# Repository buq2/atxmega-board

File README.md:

# atxmega-board

Simple pcb for atmel atxmega

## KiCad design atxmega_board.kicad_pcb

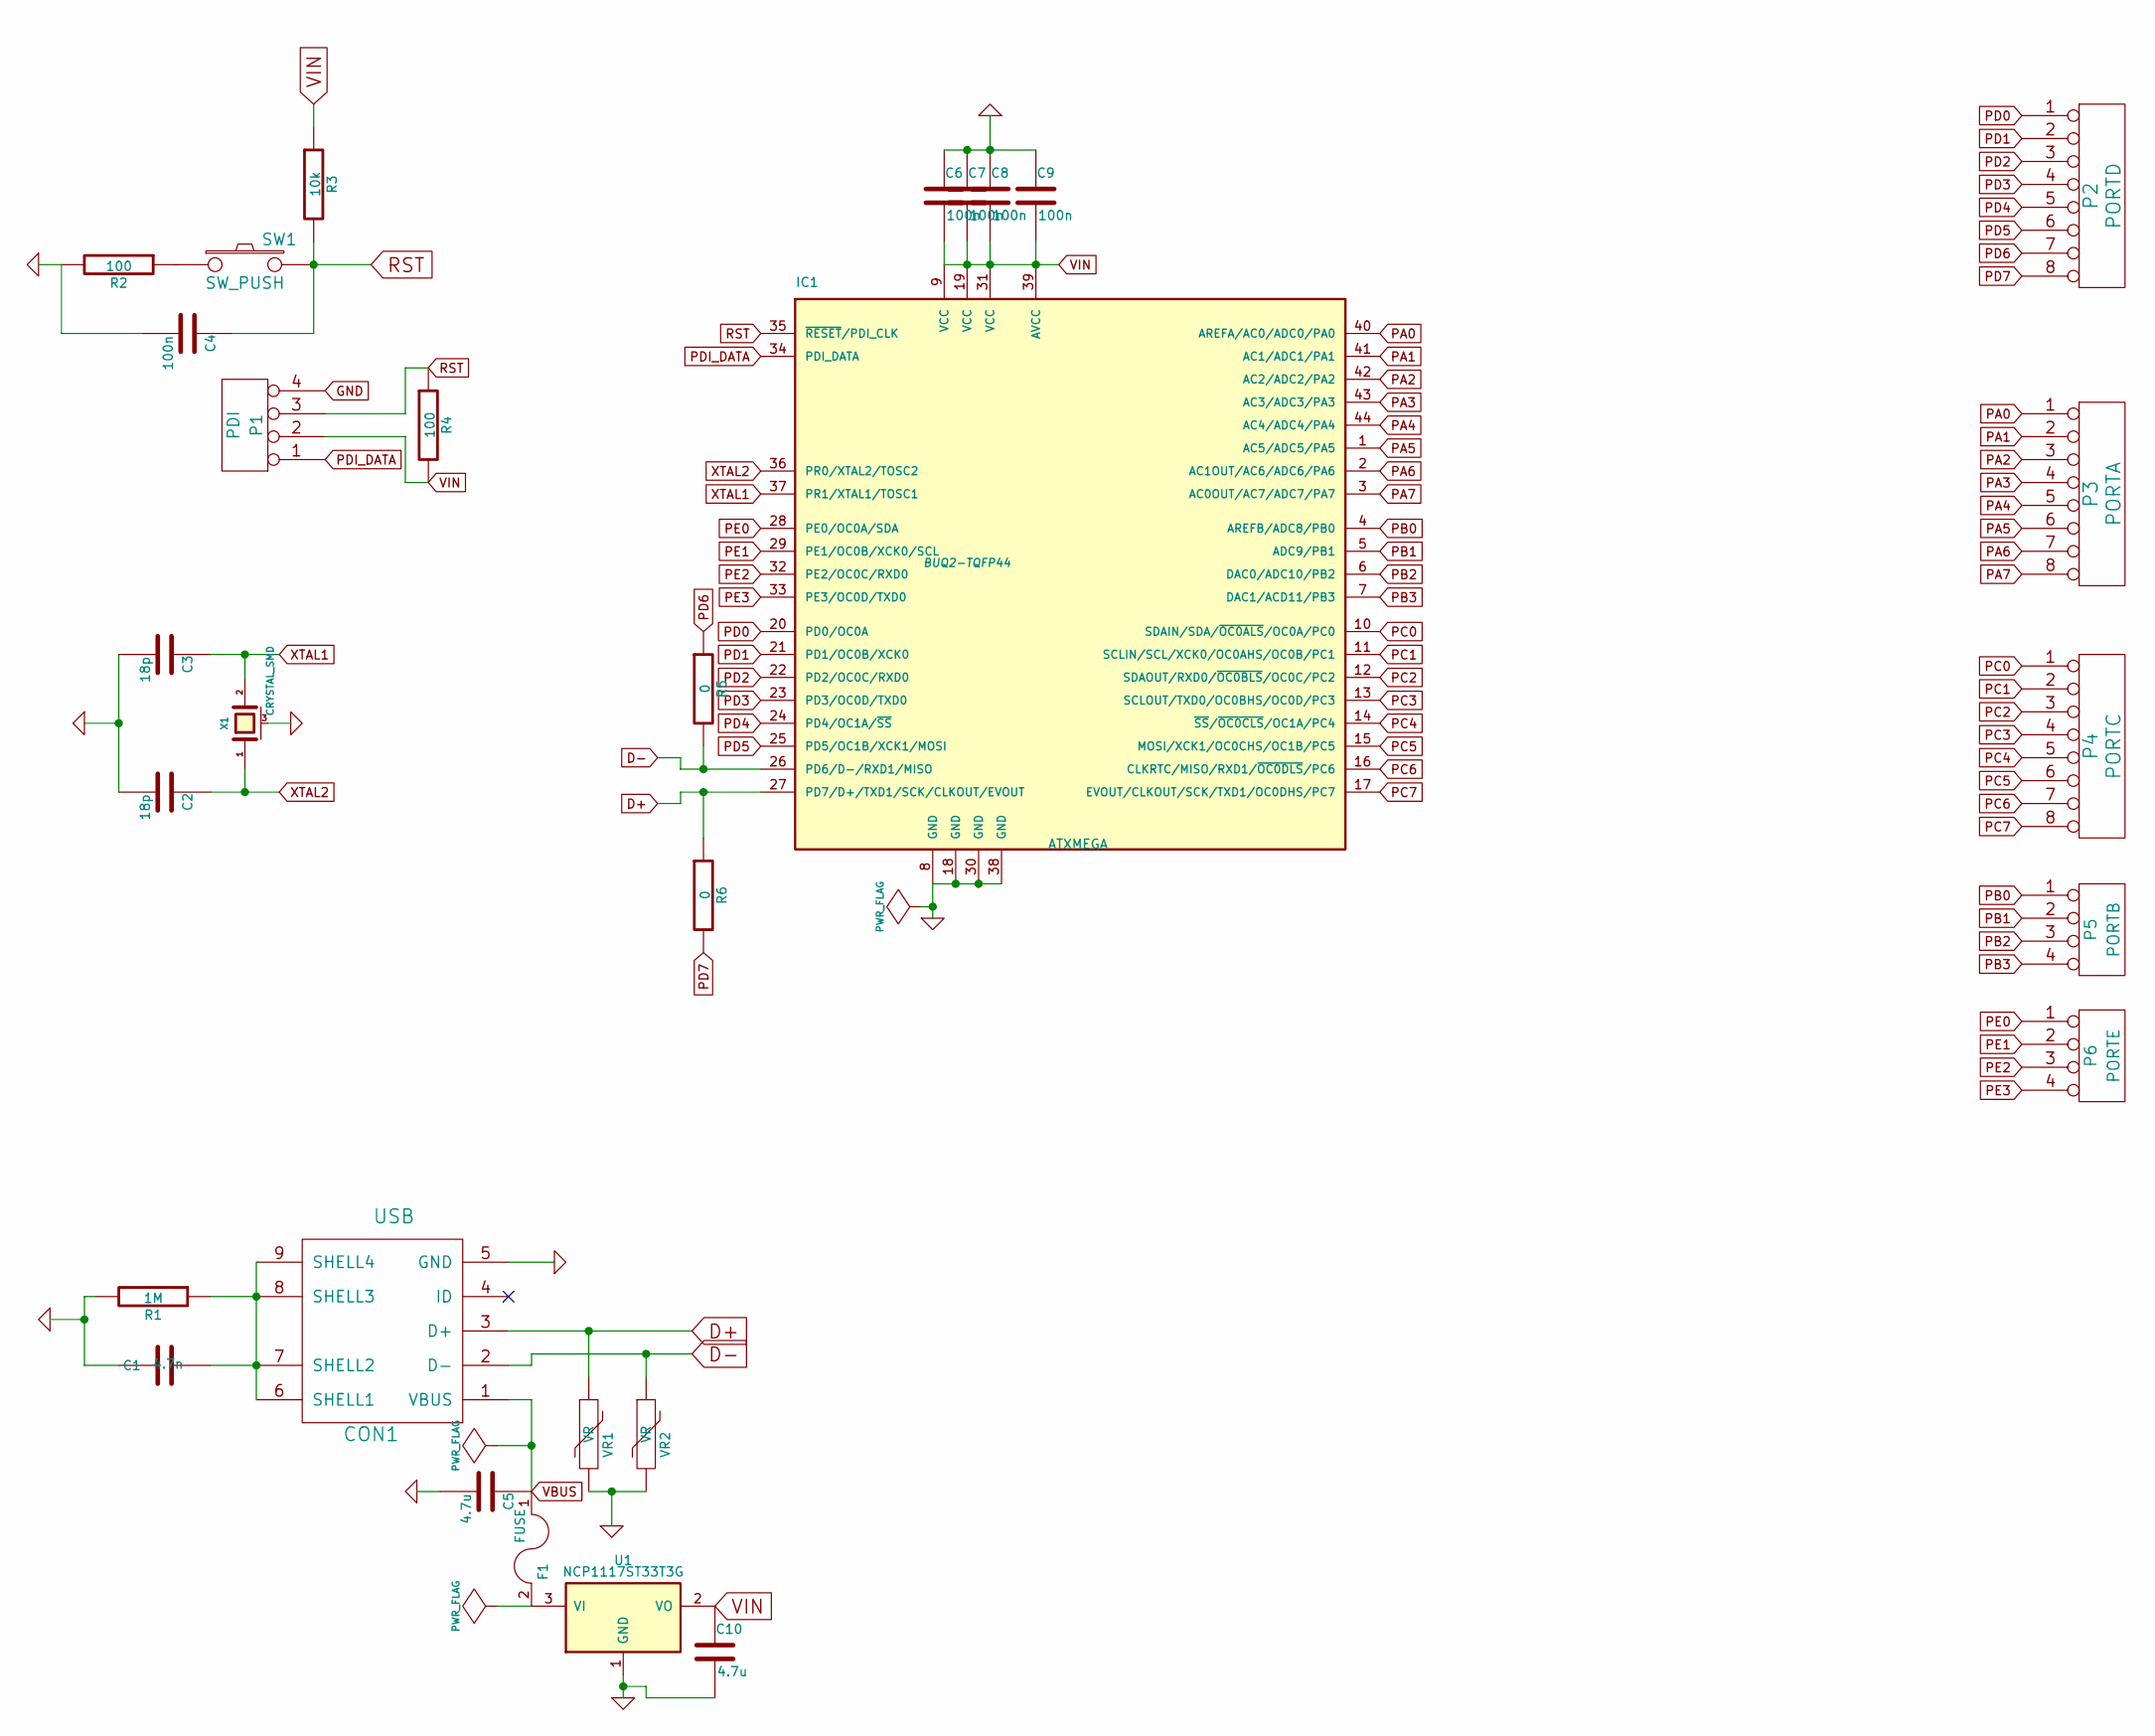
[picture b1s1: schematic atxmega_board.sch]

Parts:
C1: 4.7n; SM0603
C2, C3: 18p
C4, C6, C7, C8, C9: 100n; SM0603
C5, C10: 4.7u; SM0805
CON1: USB; BUQ2-USB-B-RIGHT-ANGLE-SM; Digikey 151-1206-1-ND
F1: FUSE
IC1: ATXMEGA; BUQ2-TQFP44
P1: PDI
P2: PORTD
P3: PORTA
P4: PORTC
P5: PORTB
P6: PORTE
R1: 1M; SM0603
R2, R4: 100; SM0603
R3: 10k; SM0603
R5, R6: 0; SM0603
SW1: SW_PUSH; PUSHBUTTON_4x4; Digikey 679-2420-2-ND (ebaysta)
U1: NCP1117ST33T3G; Digikey 1016-1237-5-ND
VR1, VR2: VR; SM0603; Digikey CG0603MLC-05E
X1: CRYSTAL_SMD; SM_CRYSTAL_4_LEAD; Digikey CTX1195CT-ND

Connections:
D+: CON1.3 (D+), IC1.27 (PD7/D+/TXD1/SCK/CLKOUT/EVOUT), R6.1, VR1.1
D-: CON1.2 (D-), IC1.26 (PD6/D-/RXD1/MISO), R5.2, VR2.1
GND: C1.1, C2.2, C3.2, C4.2, C5.2, C6.1, C7.1, C8.1, C9.1, C10.2, CON1.5 (GND), IC1.8 (GND), IC1.18 (GND), IC1.30 (GND), IC1.38 (GND), P1.4, R1.2, R2.2, U1.1 (GND), VR1.2, VR2.2, X1.3 (case)
unnamed: C1.2, CON1.6 (SHELL1), CON1.7 (SHELL2), CON1.8 (SHELL3), CON1.9 (SHELL4), R1.1
unnamed: F1.2, U1.3 (VI)
unnamed: R2.1, SW1.1
PA0: IC1.40 (AREFA/AC0/ADC0/PA0), P3.1
PA1: IC1.41 (AC1/ADC1/PA1), P3.2
PA2: IC1.42 (AC2/ADC2/PA2), P3.3
PA3: IC1.43 (AC3/ADC3/PA3), P3.4
PA4: IC1.44 (AC4/ADC4/PA4), P3.5
PA5: IC1.1 (AC5/ADC5/PA5), P3.6
PA6: IC1.2 (AC1OUT/AC6/ADC6/PA6), P3.7
PA7: IC1.3 (AC0OUT/AC7/ADC7/PA7), P3.8
PB0: IC1.4 (AREFB/ADC8/PB0), P5.1
PB1: IC1.5 (ADC9/PB1), P5.2
PB2: IC1.6 (DAC0/ADC10/PB2), P5.3
PB3: IC1.7 (DAC1/ACD11/PB3), P5.4
PC0: IC1.10 (SDAIN/SDA/~OC0ALS~/OC0A/PC0), P4.1
PC1: IC1.11 (SCLIN/SCL/XCK0/OC0AHS/OC0B/PC1), P4.2
PC2: IC1.12 (SDAOUT/RXD0/~OC0BLS~/OC0C/PC2), P4.3
PC3: IC1.13 (SCLOUT/TXD0/OC0BHS/OC0D/PC3), P4.4
PC4: IC1.14 (~SS~/~OC0CLS~/OC1A/PC4), P4.5
PC5: IC1.15 (MOSI/XCK1/OC0CHS/OC1B/PC5), P4.6
PC6: IC1.16 (CLKRTC/MISO/RXD1/~OC0DLS~/PC6), P4.7
PC7: IC1.17 (EVOUT/CLKOUT/SCK/TXD1/OC0DHS/PC7), P4.8
PD0: IC1.20 (PD0/OC0A), P2.1
PD1: IC1.21 (PD1/OC0B/XCK0), P2.2
PD2: IC1.22 (PD2/OC0C/RXD0), P2.3
PD3: IC1.23 (PD3/OC0D/TXD0), P2.4
PD4: IC1.24 (PD4/OC1A/~SS~), P2.5
PD5: IC1.25 (PD5/OC1B/XCK1/MOSI), P2.6
PD6: P2.7, R5.1
PD7: P2.8, R6.2
PDI_DATA: IC1.34 (PDI_DATA), P1.1
PE0: IC1.28 (PE0/OC0A/SDA), P6.1
PE1: IC1.29 (PE1/OC0B/XCK0/SCL), P6.2
PE2: IC1.32 (PE2/OC0C/RXD0), P6.3
PE3: IC1.33 (PE3/OC0D/TXD0), P6.4
RST: C4.1, IC1.35 (~RESET~/PDI_CLK), P1.3, R3.2, R4.1, SW1.2
VBUS: C5.1, CON1.1 (VBUS), F1.1
VIN: C6.2, C7.2, C8.2, C9.2, C10.1, IC1.9 (VCC), IC1.19 (VCC), IC1.31 (VCC), IC1.39 (AVCC), P1.2, R3.1, R4.2, U1.2 (VO)
XTAL1: C3.1, IC1.37 (PR1/XTAL1/TOSC1), X1.2
XTAL2: C2.1, IC1.36 (PR0/XTAL2/TOSC2), X1.1

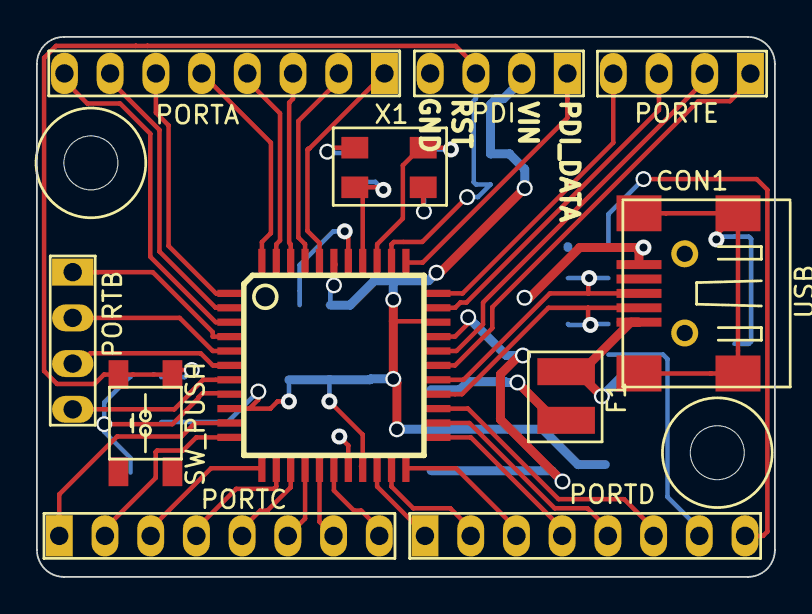
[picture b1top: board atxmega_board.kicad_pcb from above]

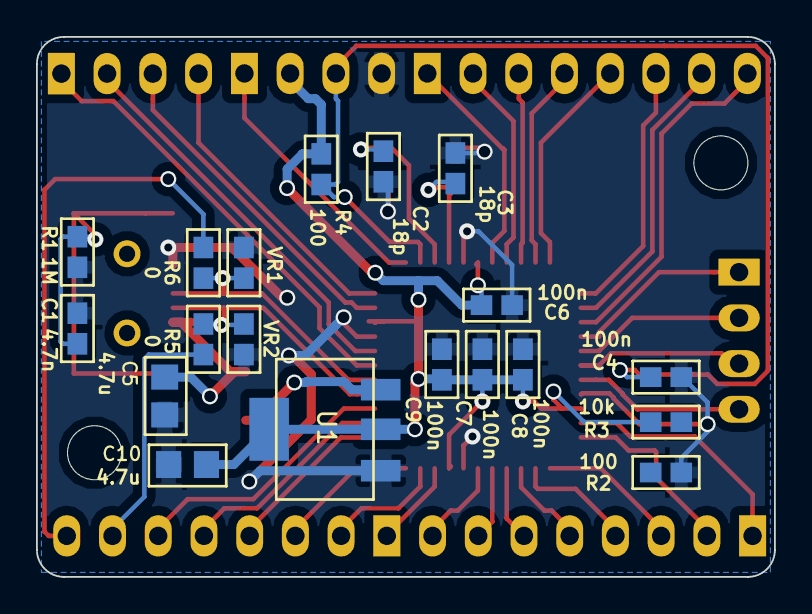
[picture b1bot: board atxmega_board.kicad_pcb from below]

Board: 2 copper layers, 41.0 x 30.0 mm, 32 parts (19 on the bottom side), 44 nets.

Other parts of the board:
MOUNTING_HOLE: VAL**; MOUNTING_HOLE
MOUNTING_HOLE#2: VAL**; MOUNTING_HOLE

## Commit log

2014-06-07 Init
2014-06-08 Round edges
2014-06-12 Ordered from OSH Park
2014-06-14 Update parts
2022-03-15 Add board images
